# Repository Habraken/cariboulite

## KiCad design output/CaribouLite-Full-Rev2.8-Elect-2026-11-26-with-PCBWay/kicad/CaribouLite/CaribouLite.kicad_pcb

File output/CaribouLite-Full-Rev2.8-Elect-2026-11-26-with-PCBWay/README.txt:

UPDATED PACKAGE: PCBWay returned files are included under pcbway/.
Read pcbway/READ-FIRST.txt for changes and production-status limits.
The original KiCad project does not include the supplier CAM changes.

CaribouLite Full Rev 2.8 — Elect investigation package
Prepared 26 November 2026

Purpose: reference design data for investigation of the reproduction board
that has no FPGA communication.

START HERE
schematics/CaribouLite-Full-Rev2.8.pdf: original released Full schematic.
  Consult the FPGA and digital-interface sheets for the communication paths.
pcb/gerber/: original released Gerber files, unchanged.
pcb/ncdrill/: original drill programs and reports, unchanged.
pcb/stack/: original PCB stack-up spreadsheet.
assembly/: original Full BOM, placement list and assembly drawing.
kicad/CaribouLite/CaribouLite.kicad_pro: converted project (KiCad 10 format),
  with PCB, all seven schematic sheets and the local footprint library.
kicad/CONVERSION-AUDIT.md: existing conversion audit; read before using KiCad.

REFERENCE STATUS
The original released PDF schematic and PCB manufacturing outputs are the
reference design data. These files are not a measured as-built record of the
faulty board or a record of any subsequent assembly substitutions or rework.

The KiCad project is supplied for inspection. The existing audit documents
schematic/PCB connectivity discrepancies, including AT86 LVDS nets and power
net naming, and incomplete imported stack-up/routing rules. It is not a
validated source for regenerating manufacturing files or updating the PCB
from the schematic. The historical audit is included unchanged; its source
paths refer to the original workspace, not this ZIP. No new electrical audit
or design changes were performed for this package.

PROVENANCE
Original PDFs, PCB and assembly data: hardware/rev2 in the local CaribouLite
repository. KiCad files: recovered-kicad/rev2.8-full local working project.
All included design files are byte-for-byte copies. Backups, session settings,
private correspondence and unrelated software are excluded.
Hardware attribution: CaribouLabs / CaribouLite; hardware/README.md identifies
the hardware license as Creative Commons Attribution 4.0 International:
https://creativecommons.org/licenses/by/4.0/

SHA256SUMS lists checksums for every included file except itself.

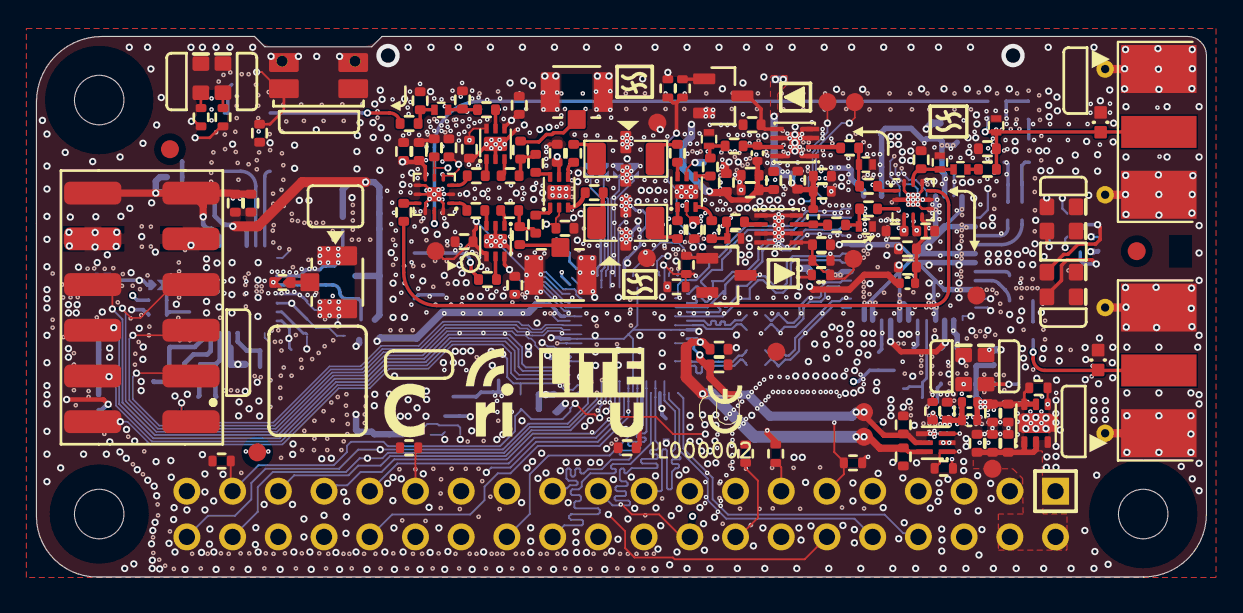
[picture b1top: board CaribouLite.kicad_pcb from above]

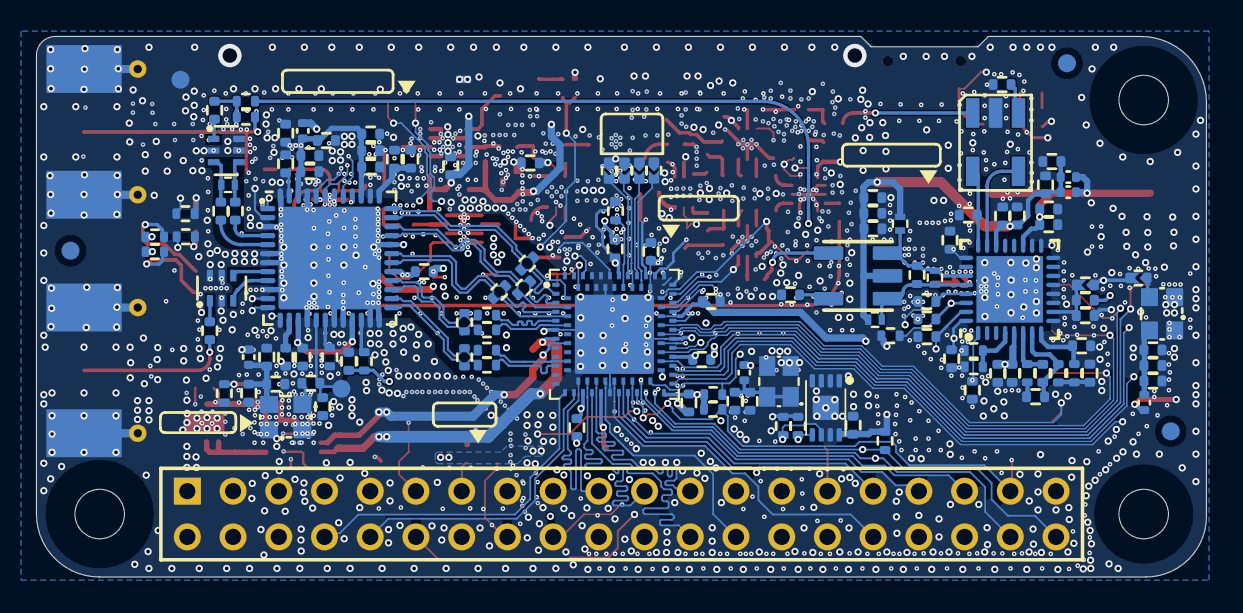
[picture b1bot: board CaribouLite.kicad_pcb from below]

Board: 4 copper layers, 65.0 x 30.0 mm, 271 parts (127 on the bottom side), 175 nets.

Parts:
C1, C2, C3, C4, C5, C6, C7, C8, C9, C10, C11, C12, C13, C14, C15, C16, C17, C18, C19, C20, C21, C22, C23, C24, C26, C27, C28, C30, C31, C33, C34, C35, C36, C37, C38, C39, C40, C41, C42, C43, C44, C45, C46, C47, C48, C49, C50, C51, C52, C53, C54, C55, C56, C57, C58, C59, C60, C61, C62, C63, C64, C65, C66, C67, C68, C69, C72, C73, C74, C76, C78, C79, C81, C82, C83, C84, C85, C86, C87, C88, C89, C90, C91, C92, C93, C94, C95, C96, C97, C98, C99, C100, C101, C102, C103, C105, C106, C107, C108, C109, C110, C111, C112, C113, C114, C115, C116, C117, C118, C119, C120, C121, C122, C123, C124, C125, C126, C127: MURATA 0402
C25, C128: 33p; MURATA 0402
C32: 10n; MURATA 0402
C70, C75, C77, C129, C130, C131, C132: 1n; MURATA 0402
C71: 100n; MURATA 0402
C80, C104: DNP; MURATA 0402
D1, D2, D7, D8, D9, D10, D11, D12: LEDC1608X35N
D3, D4: DIONC1105X44N
J1: RPI_ZERO
J2, J3: MOLEX_0732511150
J4, J5: LINX_CONUFL001-SMD-T
J6: 10129383912001ALF
J7: #NAME?; LINX_CONUFL001-SMD-T
L1, L2, L4, L5, L13, L14, L15, L19, L20: 0402 FERRITE BEAD
L3, L6, L7, L8, L9, L10, L11, L12, L16, L17: COILCRAFT 0402
L18, L21: BLM15HD182SN1D; 0402 FERRITE BEAD
L22, L23: DNP; CoilCraft 0402
MF1, MF2, MF3, MF4, MF5, MF6: FIDUCIAL_1_0_MM
R1, R2, R3, R4, R5, R6, R7, R8, R9, R10, R11, R12, R13, R15, R16, R17, R18, R19, R20, R21, R22, R23, R24, R27, R28, R29, R30, R33, R34, R36, R38, R39, R40, R41, R42, R43, R44, R45, R46, R47, R48, R49, R50, R51, R52, R57: PANASONIC 0402
R14, R35, R37: 10k; PANASONIC 0402
R25, R26: DNP; PANASONIC 0402
R31, R32: 0 Ohms; PANASONIC 0402
S1: EVQ9P701P
SH1: CARIBOULITE_EMI_BOTTOM
SH2: CARIBOULITE_EMI_TOP
TP1, TP13, TP20, TP21, TP22, TP23, TP24, TP25: TP_40
TP2: 2V5; TP_40
TP11: 5V0; TP_40
TP15, TP16, TP17: GND; TP_40
U1: QFN50P700X700X90-49N-D
U2, U4: FIL_0896BM15E0025E
U3, U29: TCXO_4_25x20
U5: SON65P200X200X80-7N
U6: SON50P150X150X80-6N
U9, U15: PDFN_2MM_8LEAD
U10, U12: FV1206
U11, U18: QFN50P200X200X60-13N-D
U13, U14, U19, U20: SON50P150X150X40-7N
U16: ICE40LP1K-QN84; LATTICE_ICE40LP1K-QN84
U21: TC4-19
U22: QFN50P500X500X85_HS-33N
U23: TC1-1-13M
U25: SG-8018CG 125.0000M-TJHPA3; SG-8018CG
U26: SON50P300X200X55-9N
U27, U28: SOT95P240X111-3N

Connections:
3V3_PG: R35.2, R37.2, U5.4, U6.1, U6.3
AT86_IRQ: J1.15, U1.40
AT86_RESET: J1.16, R10.1, U1.13
AT86_RX09_N: R18.1, U1.30, U16.B3
AT86_RX09_P: R18.2, U1.31, U16.A4
AT86_RX24_N: R13.2, U1.35, U16.A2
AT86_RX24_P: R13.1, U1.36, U16.B1
AT86_RX_CLK_N: R17.1, U1.33, U16.B2
AT86_RX_CLK_P: R17.2, U1.34, U16.A3
AT86_TX_CLK_N: R22.2, R23.1, U1.25
AT86_TX_CLK_P: R23.2, R24.2, U1.26
AT86_TX_N: R19.2, R21.1, U1.27
AT86_TX_P: R20.2, R21.2, U1.28
DPDT_1_VC1: C54.2, C56.2, TP20.1, U13.5, U14.5, U16.A33
DPDT_1_VC2: C55.2, C57.2, TP23.1, U13.2, U14.2, U16.A35
FEA09: R47.1, U1.11
FEA24: R49.1, U1.1
FEB09: R48.1, U1.12
FEB24: R50.1, U1.2
FP_CFG_0: R38.1, U16.B29
FP_CFG_1: R39.1, U16.A40
FP_CFG_2: R40.1, U16.B30
FP_CFG_3: R41.1, U16.A41
FP_TX_CLK_N: R24.1, U16.B8
FP_TX_CLK_P: R22.1, U16.A10
FP_TX_N: R20.1, U16.A5
FP_TX_P: R19.1, U16.B4
GND: C1.2, C2.1, C3.2, C4.1, C5.1, C6.1, C7.1, C8.1, C9.1, C10.1, C11.1, C14.1, C15.1, C16.1, C17.1, C18.1, C21.1, C23.1, C24.2, C25.2, C26.1, C27.1, C28.1, C30.1, C31.2, C32.2, C33.2, C34.1, C35.1, C36.1, C37.2, C38.2, C39.1, C43.1, C52.1, C53.1, C54.1, C55.1, C56.1, C57.1, C62.1, C63.2, C64.1, C65.1, C66.2, C67.2, C68.1, C69.1, C70.1, C71.1, C72.2, C73.1, C74.1, C75.1, C76.1, C77.1, C79.2, C80.2, C81.1, C82.2, C83.2, C86.1, C87.1, C88.1, C89.1, C90.1, C92.1, C93.1, C96.1, C97.1, C98.1, C99.1, C100.2, C101.2, C103.2, C104.2, C105.2, C106.2, C107.2, C108.2, C109.2, C110.2, C111.2, C112.2, C115.2, C116.2, C117.2, C118.2, C119.2, C120.1, C121.2, C123.1, C124.1, C125.2, C126.2, C127.1, C128.1, D1.C, D2.C, D3.1, D4.1, D7.C, D8.C, D9.C, D10.C, D11.C, D12.C, J1.6, J1.9, J1.14, J1.20, J1.25, J1.30, J1.34, J1.39, J2.2, J2.3, J2.4, J2.5, J2.6, J2.7, J3.2, J3.3, J3.4, J3.5, J3.6, J3.7, J4.2, J4.3, J5.2, J5.3, J6.9, J6.10, J7.2, J7.3, L6.1, L7.1, L9.1, L10.1, L11.1, L12.1, R2.1, R10.2, R11.2, R12.2, R16.2, R30.2, R38.2, R39.2, R40.2, R41.2, R57.1, S1.2, S1.3, S1.5, S1.6, TP15.1, TP16.1, TP17.1, U1.3, U1.6, U1.7, U1.10, U1.16, U1.19, U1.20, U1.23, U1.24, U1.32, U1.38, U1.45, U1.48, U1.49, U2.2, U2.5, U3.1, U3.2, U4.2, U4.5, U4.6, U5.3, U5.7, U6.4, U9.1, U9.3, U9.4, U9.6, U9.8, U9.9, U10.2, U10.4, U11.2, U11.7, U11.8, U11.10, U11.12, U11.13, U12.2, U12.4, U13.7, U14.7, U15.1, U15.3, U15.4, U15.6, U15.8, U15.9, U16.42, U16.A6, U16.A12, U16.A18, U16.A30, U16.A44, U16.B33, U16.B34, U18.2, U18.7, U18.8, U18.10, U18.12, U18.13, U19.2, U19.7, U20.2, U20.7, U22.12, U22.33, U25.2, U26.1, U26.2, U26.3, U26.4, U26.7, U26.9, U27.2, U28.2, U29.1, U29.2
GP4_SA1: J1.7, U16.A43
GP5_SA0: C103.1, J1.29, R11.1, U22.29
GP6_SOE_SE: J1.31, U16.B15
GP7_SWE_SRW: J1.26, U16.B13
GP8_SD0: J1.24, U16.A16
GP9_SD1: J1.21, U16.B11
GP10_SD2: J1.19, U16.B10
GP11_SD3: J1.23, U16.B12
GP12_SD4: J1.32, U16.B14
GP13_SD5: J1.33, U16.A20
GP14_SD6: J1.8, U16.A13
GP15_SD7: J1.10, U16.A14
ICE_CDONE: J1.13, R15.1, U16.B16
ICE_CRESET: J1.37, R12.1, R14.1, U16.A21
ICE_FP_SCK: C105.1, J1.40, R27.1, U1.41, U16.A23, U22.31
ICE_FP_SS_B: J1.12, R28.1, U16.B18
LED4: R51.1, U16.A39
LED5: R52.1, U16.A38
LFILT1: C114.2, R36.1, U22.6
LFILT2: C113.1, C114.1, R34.2, U22.7
LFILT3: C109.1, R33.1, U22.8
MOD_BYPASS: C84.1, U18.9
MOD_RX: C78.2, U19.3
MOD_TX: C85.2, U20.1
MXR_ENBL: C125.1, U16.B22, U22.1
MXR_FM: C126.1, U16.A32, U22.25
MXR_VCC_3V3: C75.2, C81.2, U18.6
MXR_VDDA: C79.1, C87.2, C88.2, C89.2, C104.1, C115.1, C116.1, C117.1, C118.1, L15.2, L21.2, L22.1, L23.1, U21.2, U22.5, U22.22
NetC2_2: C2.2, C3.1, U1.37
NetC11_2: C11.2, C102.1, R1.2
NetC12_1: C12.1, L3.2, U2.4
NetC13_1: C13.1, C18.2, TP1.1, U1.17
NetC13_2: C13.2, U3.3
NetC14_2: C14.2, U1.47
NetC15_2: C15.2, C16.2, C17.2, L2.1, U3.4
NetC19_1: C19.1, R31.1, R32.1
NetC19_2: C19.2, U2.1
NetC20_1: C20.1, L3.1, U2.3
NetC21_2: C21.2, U1.14
NetC22_1: C22.1, D3.2, J2.1
NetC22_2: C22.2, U4.1
NetC27_2: C27.2, L14.2, L20.2, R37.1, U6.2
NetC40_1: C40.1, C48.1, C49.2
NetC40_2: C40.2, J4.1
NetC41_1: C41.1, C45.2, L6.2
NetC41_2: C41.2, L5.2, U9.7
NetC42_1: C42.1, C46.2, L7.2
NetC42_2: C42.2, U9.2
NetC43_2: C43.2, U9.5, U27.3
NetC44_1: C44.1, C50.1, C51.2
NetC44_2: C44.2, J5.1
NetC45_1: C45.1, U14.4
NetC46_1: C46.1, U11.1
NetC47_1: C47.1, L8.2
NetC47_2: C47.2, C53.2, D4.2, J3.1, L9.2, R31.2
NetC48_2: C48.2, U19.1
NetC49_1: C49.1, U13.1
NetC50_2: C50.2, U20.3
NetC51_1: C51.1, U13.6
NetC52_2: C52.2, L8.1, L10.2, U11.11
NetC58_1: C58.1, C60.2, L11.2
NetC58_2: C58.2, U14.3
NetC59_1: C59.1, C61.2, L12.2
NetC59_2: C59.2, U11.3
NetC60_1: C60.1, U15.2
NetC61_1: C61.1, L13.2, U15.7
NetC62_2: C62.2, R4.2, R57.2, TP25.1, U15.5, U28.3
NetC70_2: C70.2, C71.2, L18.1, U25.1, U25.4
NetC78_1: C78.1, U18.1
NetC84_2: C84.2, U11.9
NetC85_1: C85.1, U18.3
NetC91_1: C91.1, U19.5
NetC91_2: C91.2, U21.6
NetC92_2: C92.2, U22.24, U23.6
NetC94_1: C94.1, C97.2, L17.1
NetC94_2: C94.2, U23.1
NetC95_1: C95.1, U20.5
NetC95_2: C95.2, C98.2, L17.2
NetC100_1: C100.1, U21.4
NetC101_1: C101.1, U23.3
NetC102_2: C102.2, C108.1, C122.1, U22.10
NetC110_1: C110.1, R33.2, R34.1
NetC113_2: C113.2, R36.2
NetC122_2: C122.2, R25.2, R26.1
NetC123_2: C123.2, C124.2, C128.2, L19.1, U29.4
NetC129_1: C129.1, U10.1
NetC129_2: C129.2, U13.3
NetC130_1: C130.1, U10.3
NetC130_2: C130.2, U14.1
NetC131_1: C131.1, U12.1
NetC131_2: C131.2, U13.4
NetC132_1: C132.1, U12.3
NetC132_2: C132.2, U14.6
NetD1_A: D1.A, R7.2
NetD2_A: D2.A, R6.2
NetD7_A: D7.A, R47.2
NetD8_A: D8.A, R48.2
NetD9_A: D9.A, R49.2
NetD10_A: D10.A, R50.2
NetD11_A: D11.A, R51.2
NetD12_A: D12.A, R52.2
NetJ7_1: J7.1, R25.1
NetL16_1: L16.1, L23.2, R29.1, U21.1, U22.27
NetL16_2: L16.2, L22.2, R29.2, U21.3, U22.28
NetR1_1: R1.1, U1.22
NetR2_2: R2.2, U1.18
NetR16_1: R16.1, R30.1, U22.4
NetR26_2: R26.2, U29.3
NetR32_2: R32.2, U18.11
NetR45_1: R45.1, U27.1
NetR46_1: R46.1, U28.1
NetU16_A29: U16.A29, U25.3
NetU22_23: U22.23, U23.4
PMOD_IO1: J6.1, U16.B24
PMOD_IO2: J6.3, U16.A31
PMOD_IO3: J6.5, U16.B23
PMOD_IO4: J6.7, U16.B21
PMOD_IO5: J6.2, U16.A25
PMOD_IO6: J6.4, U16.A26
PMOD_IO7: J6.6, U16.A27
PMOD_IO8: J6.8, U16.B20
RF09_N: U1.9, U4.3
RF09_P: U1.8, U4.4
RF24_N: C20.2, U1.5
RF24_P: C12.2, U1.4
RFFE_3V3: C36.2, C77.2, L4.2, U11.6
RFFE_5V: C23.2, C24.1, C31.1, C63.1, C64.2, C65.2, C127.2, J1.2, J1.4, L13.1, R6.1, TP11.1, U5.1, U5.2
RFFE_LNA_VCC: C25.1, C26.2, C33.1, C34.2, C35.2, C39.2, C72.1, C73.2, C74.2, C80.1, C86.2, C111.1, C112.1, C119.1, C121.1, J6.11, J6.12, L1.1, L4.1, L5.1, L14.1, L15.1, L18.2, L19.2, L20.1, L21.1, R3.2, R5.2, R7.1, R8.1, R9.1, R14.2, R15.2, R27.2, R28.2, R35.1, R42.2, R43.1, R44.1, U5.5, U5.6, U16.A17, U16.A24, U16.A42, U16.B25, U22.19, U26.8
RF_TR_VC1: C37.1, C82.1, C90.2, C99.2, TP21.1, U11.4, U16.A34, U18.4, U19.6, U20.6
RF_TR_VC2: C38.1, C83.1, TP22.1, U11.5, U16.B26, U18.5
RPI_INTER_SCL: J1.28, R43.2, U26.6
RPI_INTER_SDA: J1.27, R44.2, U26.5
RPI_MISO: J1.35, U1.44, U16.B17
RPI_MOSI: C106.1, J1.38, U1.43, U16.A22, U22.32
RPI_SS_AT86: J1.11, R3.1, U1.42
RPI_SS_MXR: C107.1, J1.36, R5.1, U22.30
RXMODE: C93.2, C96.2, TP24.1, U16.B27, U19.4, U20.4
SHDN_RX_LNA: R9.2, R45.2, U16.A46
SHDN_TX_LNA: R4.1, R8.2, R46.2, U16.B36
SMI_READ_REQ: J1.18, U16.B19
SMI_SA2: J1.5, U16.A48
SMI_SA3: J1.3, U16.A47
SMI_WRITE_REQ: J1.22, U16.A19
USR_SW: C76.2, R42.1, S1.4, U16.B31
VCC_1V2: C30.2, C66.1, C67.1, C68.2, C69.2, TP13.1, U6.6, U16.A7, U16.A15, U16.A28, U16.B28
VCC_2V5: C28.2, C120.2, TP2.1, U6.5, U16.A36, U16.B6
VCC_ANA: C1.1, C4.2, C5.2, C6.2, C7.2, C8.2, C9.2, C10.2, C32.1, L1.2, L2.2, U1.15, U1.21, U1.29, U1.39, U1.46
